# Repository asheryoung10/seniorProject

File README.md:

# Senior Project

## Goal

The goal of this project is to collect high-quality image data from a portable stereo vision device. The recorded data will later be used with a SLAM algorithm to determine the trajectory of the device.

The project is focused on building a complete prototype capable of collecting the sensor data needed for reliable trajectory estimation.

## Current Progress

- Prototype parts have been selected.
- The physical device and housing have been designed and refined through multiple iterations.
- The stereo camera setup has been assembled.
- Stereo image capture is working.
- The data collection software is still being refined.
- Current development is focused on collecting IMU data at the same time as the stereo images without losing capture speed.
- Once reliable data collection is complete, the collected data will be used with a SLAM algorithm to determine the trajectory of the device.

## Prototype

The device is built around a Raspberry Pi and a pair of stereo cameras.

The housing is custom designed to hold the cameras, Raspberry Pi, and other components in a compact package.

## Housing Development

The housing has gone through several design iterations as the physical layout and component placement have been refined.

The final housing is 3D printed and designed using CAD software.

The `CAD` folder contains the FreeCAD project files and 3MF models used to design and manufacture the housing.

## Data Collection

The `Capture` folder contains the software responsible for collecting stereo image and IMU data.

The stereo cameras are used to capture image data while the IMU provides motion information from the device. A major part of the current development is getting both data sources to operate at the same time without significantly reducing the image capture rate.

The folder also contains the camera triggering and `libcamera` configuration used by the stereo camera system.

The goal is to produce consistent, high-quality synchronized data that can later be passed into a SLAM algorithm.

## Viewer

The `Viewer` folder contains software for viewing and inspecting recorded data.

The viewer is used to inspect the captured stereo imagery and verify that the collected data is usable.

## Screen Flash

The `screenFlashBlackWhite` folder contains the software used to control the screen flashing component of the system.

The screen flash is part of the timing and synchronization system used during data collection.

## Project Structure

The repository is organized into the following main components:

- `CAD` contains the FreeCAD project files and 3MF models for the device housing.
- `Capture` contains the stereo camera, IMU, triggering, and data collection software.
- `Pictures` contains project photos, demonstrations, and other visual documentation.
- `Viewer` contains software for viewing and inspecting recorded data.
- `screenFlashBlackWhite` contains the screen flashing software used for synchronization.

## Project Status

The prototype hardware parts have been selected and the physical device is being refined.

The main software task currently underway is improving the data collection system so that IMU data can be collected concurrently with stereo images without sacrificing capture speed.

After the data collection system is sufficiently reliable, the next major stage of the project will be to run a SLAM algorithm on the collected data to estimate the trajectory of the device.

## Pictures
First Model

Superglued together, with cameras that required software rotation and were oriented vertically instead of horizontally.

Handheld demonstration of the old shell with the original viewing software. Capture rate was less than 30 Hz.

Case Development

Multiple case designs were tested before settling on the final clamshell design.

Final Clamshell Design

CAD design of the final device housing.

3D-printed version of the final housing.

Software

Current viewing tool.

Work in progress: rotation collection using the IMU6050.

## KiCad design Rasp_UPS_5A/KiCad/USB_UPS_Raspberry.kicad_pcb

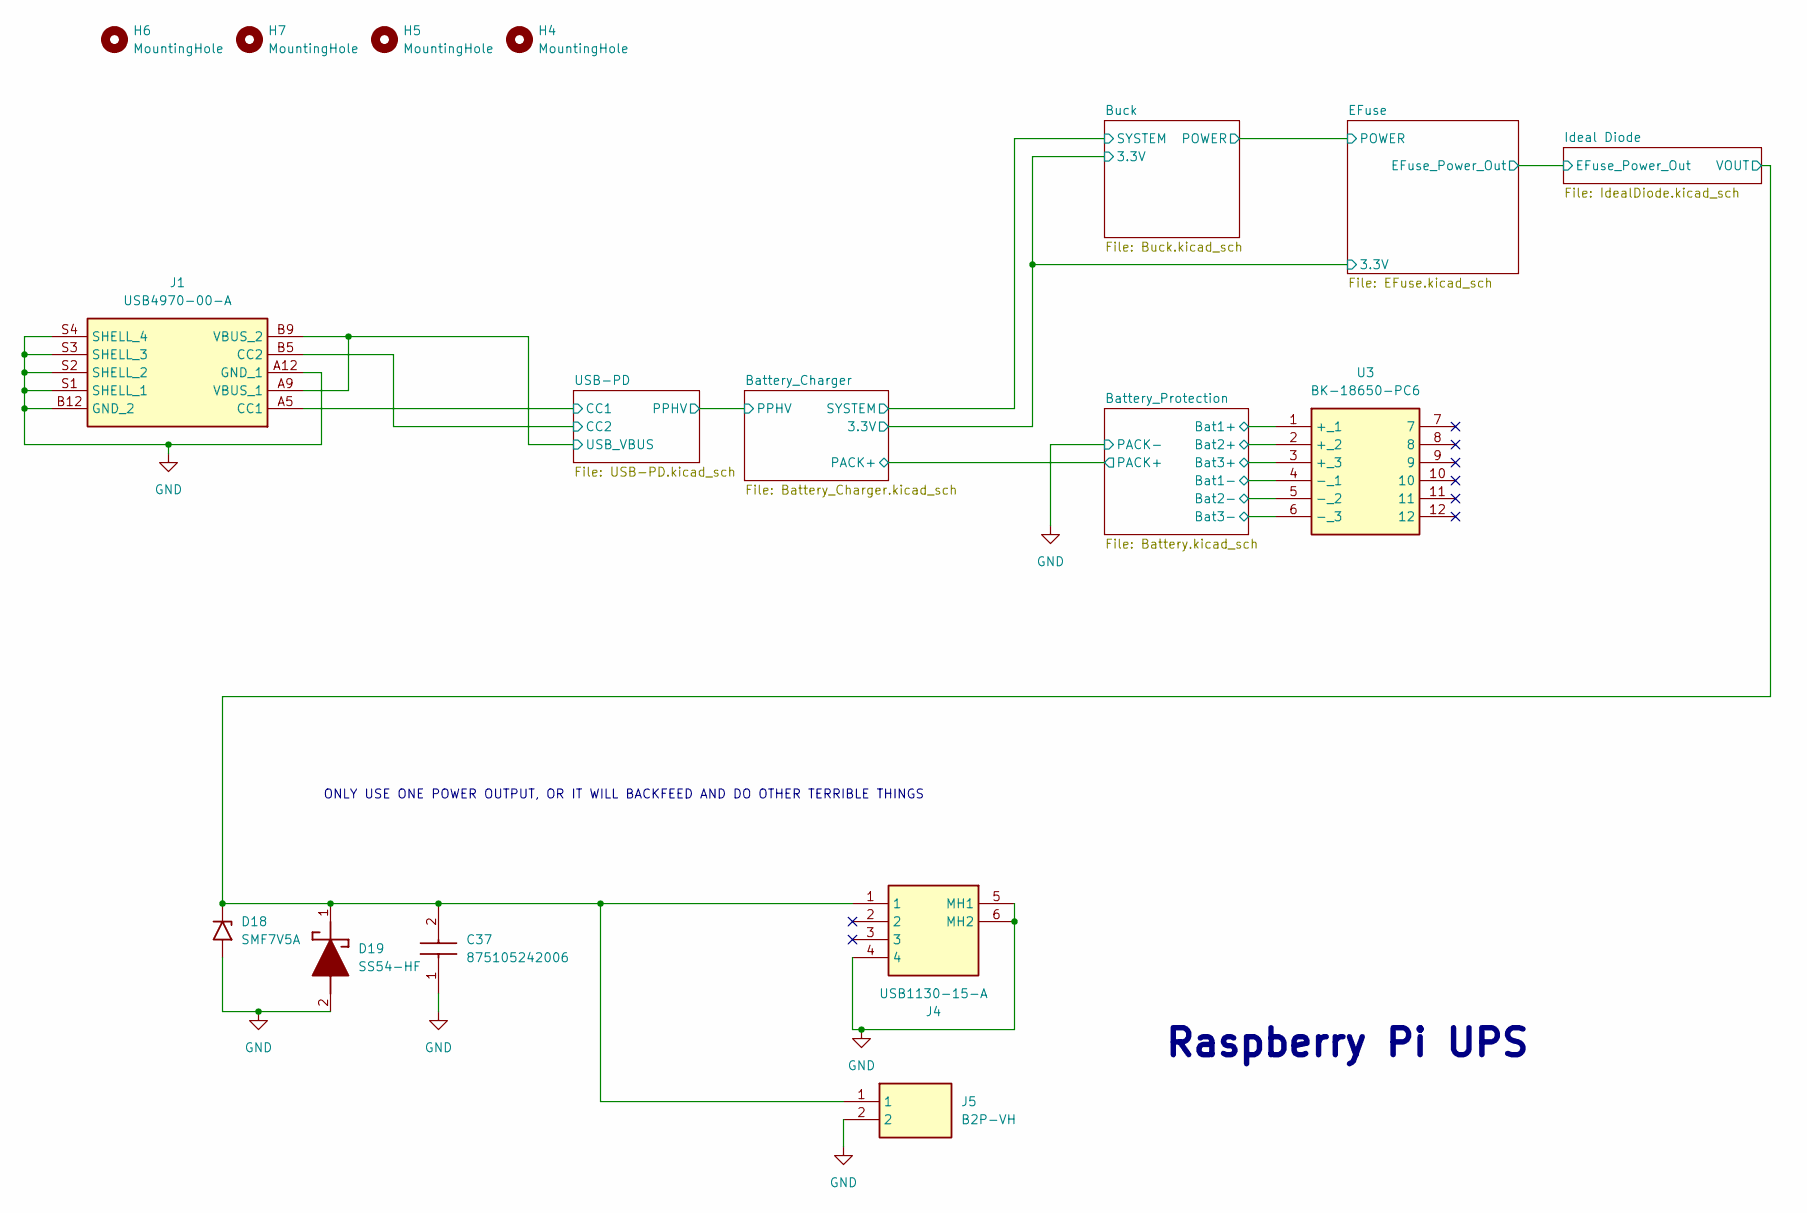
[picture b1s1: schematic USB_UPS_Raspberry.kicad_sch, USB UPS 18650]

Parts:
C37: 875105242006; CAPAE530X550N; Mouser Part Number 710-875105242006
D18: SMF7V5A; D_SMF
D19: SS54-HF; DIOM5025X220N; Mouser Part Number 750-SS54-HF
H4, H5, H6, H7: MountingHole; MountingHole_3.2mm_M3_Pad
J1: USB4970-00-A; USB497000A; Manufacturer_Part_Number USB4970-00-A
J4: USB1130-15-A; USB113015A; Mouser Part Number 640-USB1130-15-A
J5: B2P-VH; SHDR2W114P0X396_1X2_786X850X940P; Manufacturer_Part_Number B2P-VH
U3: BK-18650-PC6; BK18650PC6; Manufacturer_Part_Number BK-18650-PC6

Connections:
-BATT: U3.4 (-_1); also elsewhere on the board
/Battery_Charger/PACK+: U3.3 (+_3); also elsewhere on the board
/Battery_Protection/Bat1+: U3.1 (+_1), U3.5 (-_2); also elsewhere on the board
/Battery_Protection/Bat2+: U3.2 (+_2), U3.6 (-_3); also elsewhere on the board
/Ideal Diode/VOUT: C37.2 (-), D18.1 (A1), D19.1 (K), J4.1, J5.1; also elsewhere on the board
/USB-PD/CC1: J1.A5 (CC1); also elsewhere on the board
/USB-PD/CC2: J1.B5 (CC2); also elsewhere on the board
/USB-PD/VBUS: J1.A9 (VBUS_1), J1.B9 (VBUS_2); also elsewhere on the board
GND: C37.1 (+), D18.2 (A2), D19.2 (A), J1.A12 (GND_1), J1.B12 (GND_2), J1.S1 (SHELL_1), J1.S2 (SHELL_2), J1.S3 (SHELL_3), J1.S4 (SHELL_4), J4.4, J4.5 (MH1), J4.6 (MH2), J5.2; also elsewhere on the board

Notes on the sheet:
ONLY USE ONE POWER OUTPUT, OR IT WILL BACKFEED AND DO OTHER TERRIBLE THINGS
Raspberry Pi UPS

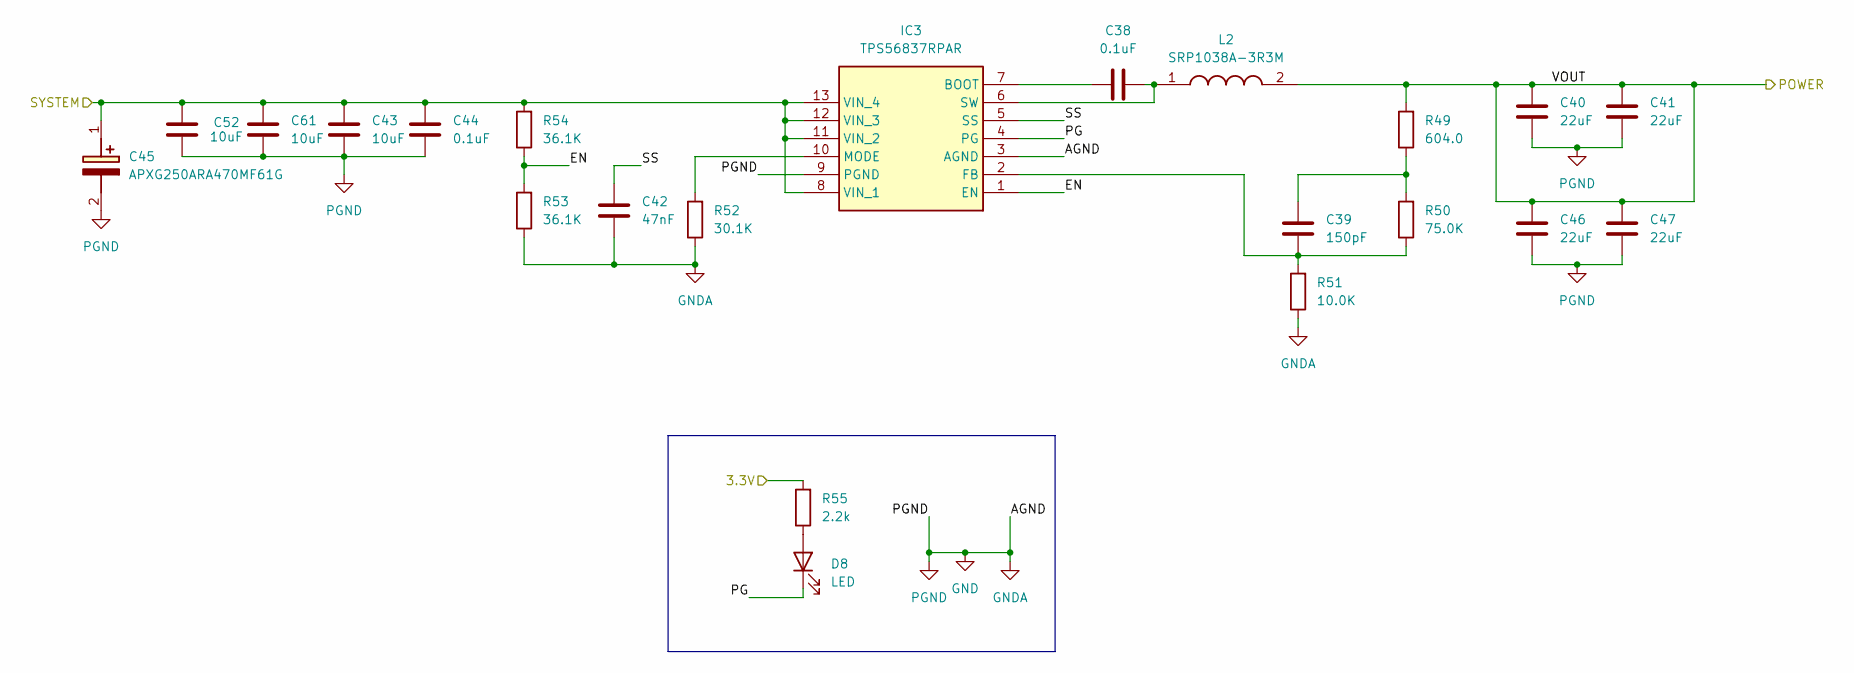
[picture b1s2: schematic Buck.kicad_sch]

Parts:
C38, C44: 0.1uF; C_0805_2012Metric
C39: 150pF; C_0805_2012Metric
C40, C41, C46, C47: 22uF; C_0805_2012Metric
C42: 47nF; C_0805_2012Metric
C43, C52, C61: 10uF; C_0805_2012Metric
C45: APXG250ARA470MF61G; CAPAE660X610N; Manufacturer_Part_Number APXG250ARA470MF61G; Mouser Part Number 661-APXG250A470MF61G
D8: LED; LED_0805_2012Metric
IC3: TPS56837RPAR; TPS56A37RPAR; Mouser Part Number 595-TPS56837RPAR
L2: SRP1038A-3R3M; INDPM110100X400N; Manufacturer_Part_Number SRP1038A-3R3M; Mouser Part Number 652-SRP1038A-3R3M
R49: 604.0; R_0805_2012Metric
R50: 75.0K; R_0805_2012Metric
R51: 10.0K; R_0805_2012Metric
R52: 30.1K; R_0805_2012Metric
R53, R54: 36.1K; R_0805_2012Metric
R55: 2.2k; R_0805_2012Metric

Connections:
/Battery_Charger/SYSTEM: C43.1, C44.1, C45.1 (+), C52.1, C61.1, IC3.8 (VIN_1), IC3.11 (VIN_2), IC3.12 (VIN_3), IC3.13 (VIN_4), R54.2; also elsewhere on the board
/Battery_Charger/VREF: R55.2; also elsewhere on the board
/Buck/EN: IC3.1 (EN), R53.2, R54.1
/Buck/PG: D8.1 (K), IC3.4 (PG)
/Buck/SS: C42.1, IC3.5 (SS)
/Buck/VOUT: C40.2, C41.2, C46.2, C47.2, L2.2, R49.2; also elsewhere on the board
GND: C40.1, C41.1, C42.2, C43.2, C44.2, C45.2 (-), C46.1, C47.1, C52.2, C61.2, IC3.3 (AGND), IC3.9 (PGND), R51.1, R52.1, R53.1; also elsewhere on the board
unnamed: C39.2, R49.1, R50.2
unnamed: D8.2 (A), R55.1
unnamed: C38.1, IC3.7 (BOOT)
unnamed: C39.1, IC3.2 (FB), R50.1, R51.2
unnamed: IC3.10 (MODE), R52.2
unnamed: C38.2, IC3.6 (SW), L2.1

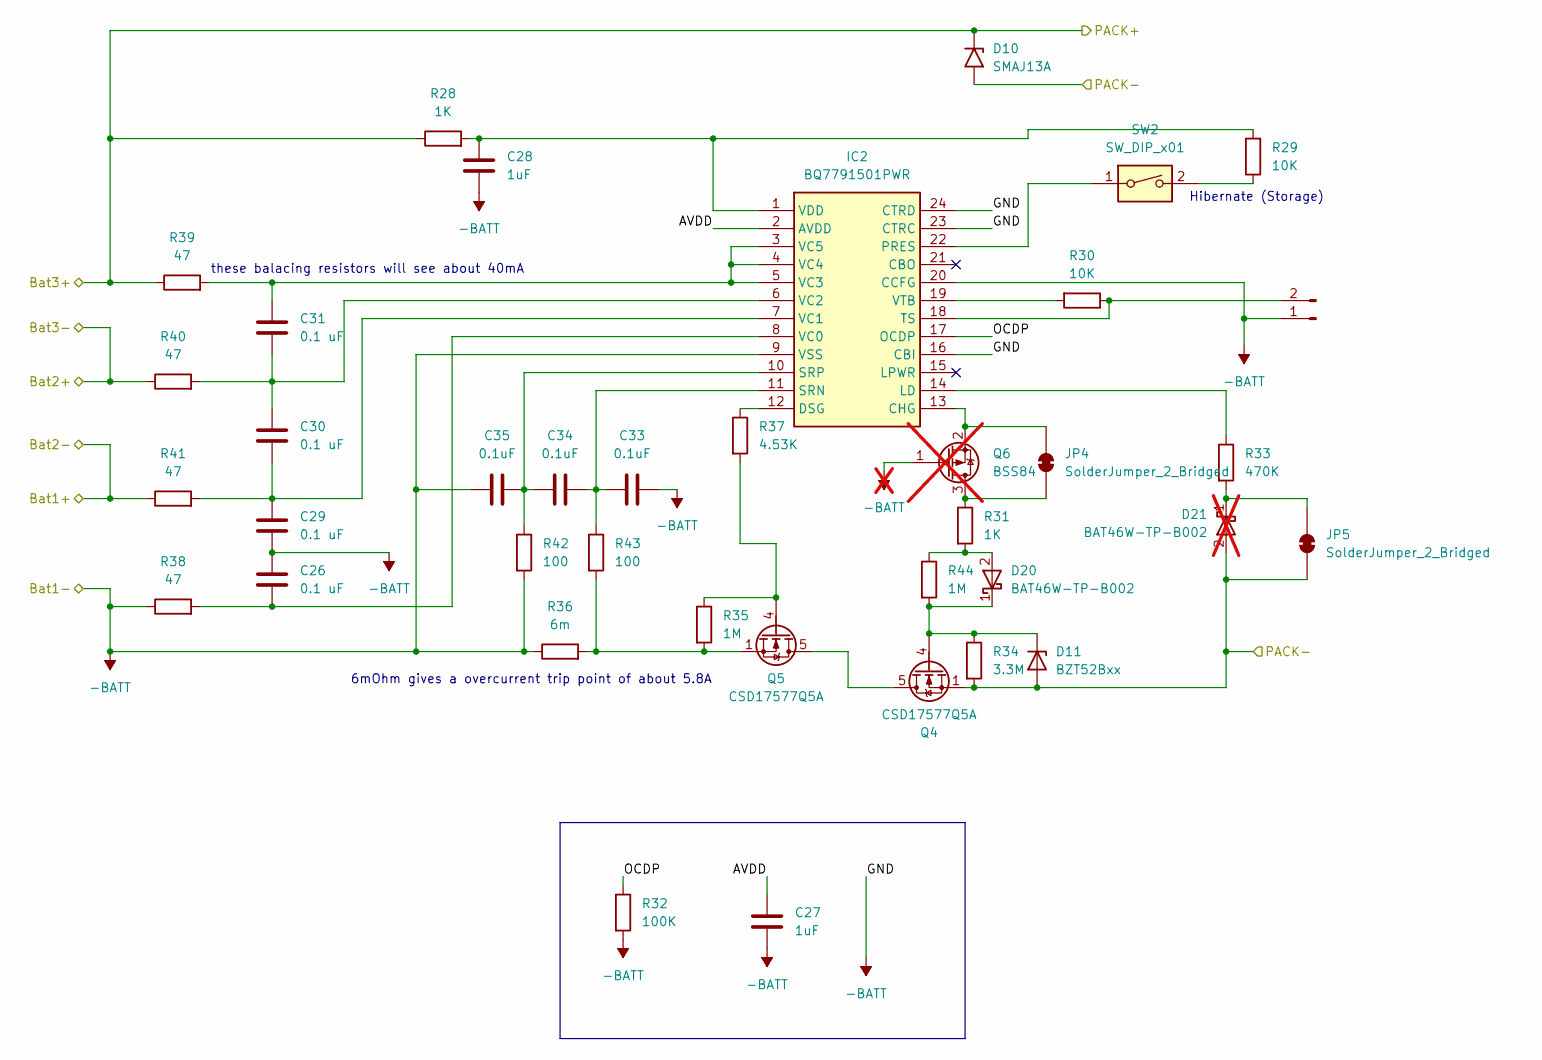
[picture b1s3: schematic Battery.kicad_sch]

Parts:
C26, C29, C30, C31: 0.1 uF; C_0805_2012Metric
C27, C28: 1uF; C_0805_2012Metric
C33, C34, C35: 0.1uF; C_0805_2012Metric
D10: SMAJ13A; D_SMA
D11: BZT52Bxx; D_SOD-123F
D20: BAT46W-TP-B002; SOD3716X135N; Manufacturer_Part_Number BAT46W-TP-B002
D21: BAT46W-TP-B002; SOD3716X135N; Manufacturer_Part_Number BAT46W-TP-B002; not fitted
IC2: BQ7791501PWR; SOP65P640X120-24N; Mouser Part Number 595-BQ7791501PWR
J3: Conn_01x02_Pin; PinHeader_1x02_P2.54mm_Vertical
JP4, JP5: SolderJumper_2_Bridged; SolderJumper-2_P1.3mm_Bridged_Pad1.0x1.5mm
Q4, Q5: CSD17577Q5A; TDSON-8-1
Q6: BSS84; SOT-23; not fitted
R28, R31: 1K; R_0805_2012Metric
R29, R30: 10K; R_0805_2012Metric
R32: 100K; R_0805_2012Metric
R33: 470K; R_0805_2012Metric
R34: 3.3M; R_0805_2012Metric
R35, R44: 1M; R_0805_2012Metric
R36: 6m; R_1206_3216Metric
R37: 4.53K; R_0805_2012Metric
R38, R39, R40, R41: 47; R_1206_3216Metric
R42, R43: 100; R_0805_2012Metric
SW2: SW_DIP_x01; SW_DIP_SPSTx01_Slide_6.7x4.1mm_W7.62mm_P2.54mm_LowProfile

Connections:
-BATT: C26.1, C27.2, C28.2, C29.2, C33.2, C35.1, IC2.9 (VSS), IC2.16 (CBI), IC2.20 (CCFG), IC2.23 (CTRC), IC2.24 (CTRD), J3.1, Q6.1 (G), R32.2, R36.1, R38.1, R42.2; also elsewhere on the board
/Battery_Charger/PACK+: D10.1 (A1), R28.1, R39.1; also elsewhere on the board
/Battery_Protection/AVDD: C27.1, IC2.2 (AVDD)
/Battery_Protection/Bat1+: R41.1; also elsewhere on the board
/Battery_Protection/Bat2+: R40.1; also elsewhere on the board
/Battery_Protection/OCDP: IC2.17 (OCDP), R32.1
GND: D10.2 (A2), D11.2 (A), D21.2 (A), JP5.1 (A), Q4.1 (S), Q4.2 (S), Q4.3 (S), R34.2; also elsewhere on the board
unnamed: D11.1 (K), D20.1 (K), Q4.4 (G), R34.1, R44.2
unnamed: D20.2 (A), R31.2, R44.1
unnamed: D21.1 (K), JP5.2 (B), R33.2
unnamed: IC2.13 (CHG), JP4.2 (B), Q6.2 (S)
unnamed: IC2.12 (DSG), R37.1
unnamed: IC2.14 (LD), R33.1
unnamed: IC2.22 (PRES), SW2.1
unnamed: C33.1, C34.2, IC2.11 (SRN), R43.1
unnamed: C34.1, C35.2, IC2.10 (SRP), R42.1
unnamed: IC2.18 (TS), J3.2, R30.1
unnamed: C26.2, IC2.8 (VC0), R38.2
unnamed: C29.1, C30.2, IC2.7 (VC1), R41.2
unnamed: C30.1, C31.2, IC2.6 (VC2), R40.2
unnamed: C31.1, IC2.3 (VC5), IC2.4 (VC4), IC2.5 (VC3), R39.2
unnamed: C28.1, IC2.1 (VDD), R28.2, R29.2
unnamed: IC2.19 (VTB), R30.2
unnamed: JP4.1 (A), Q6.3 (D), R31.1
unnamed: Q4.5 (D), Q5.5 (D)
unnamed: Q5.4 (G), R35.1, R37.2
unnamed: Q5.1 (S), Q5.2 (S), Q5.3 (S), R35.2, R36.2, R43.2
unnamed: R29.1, SW2.2

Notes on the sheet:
Hibernate (Storage)
these balacing resistors will see about 40mA
6mOhm gives a overcurrent trip point of about 5.8A

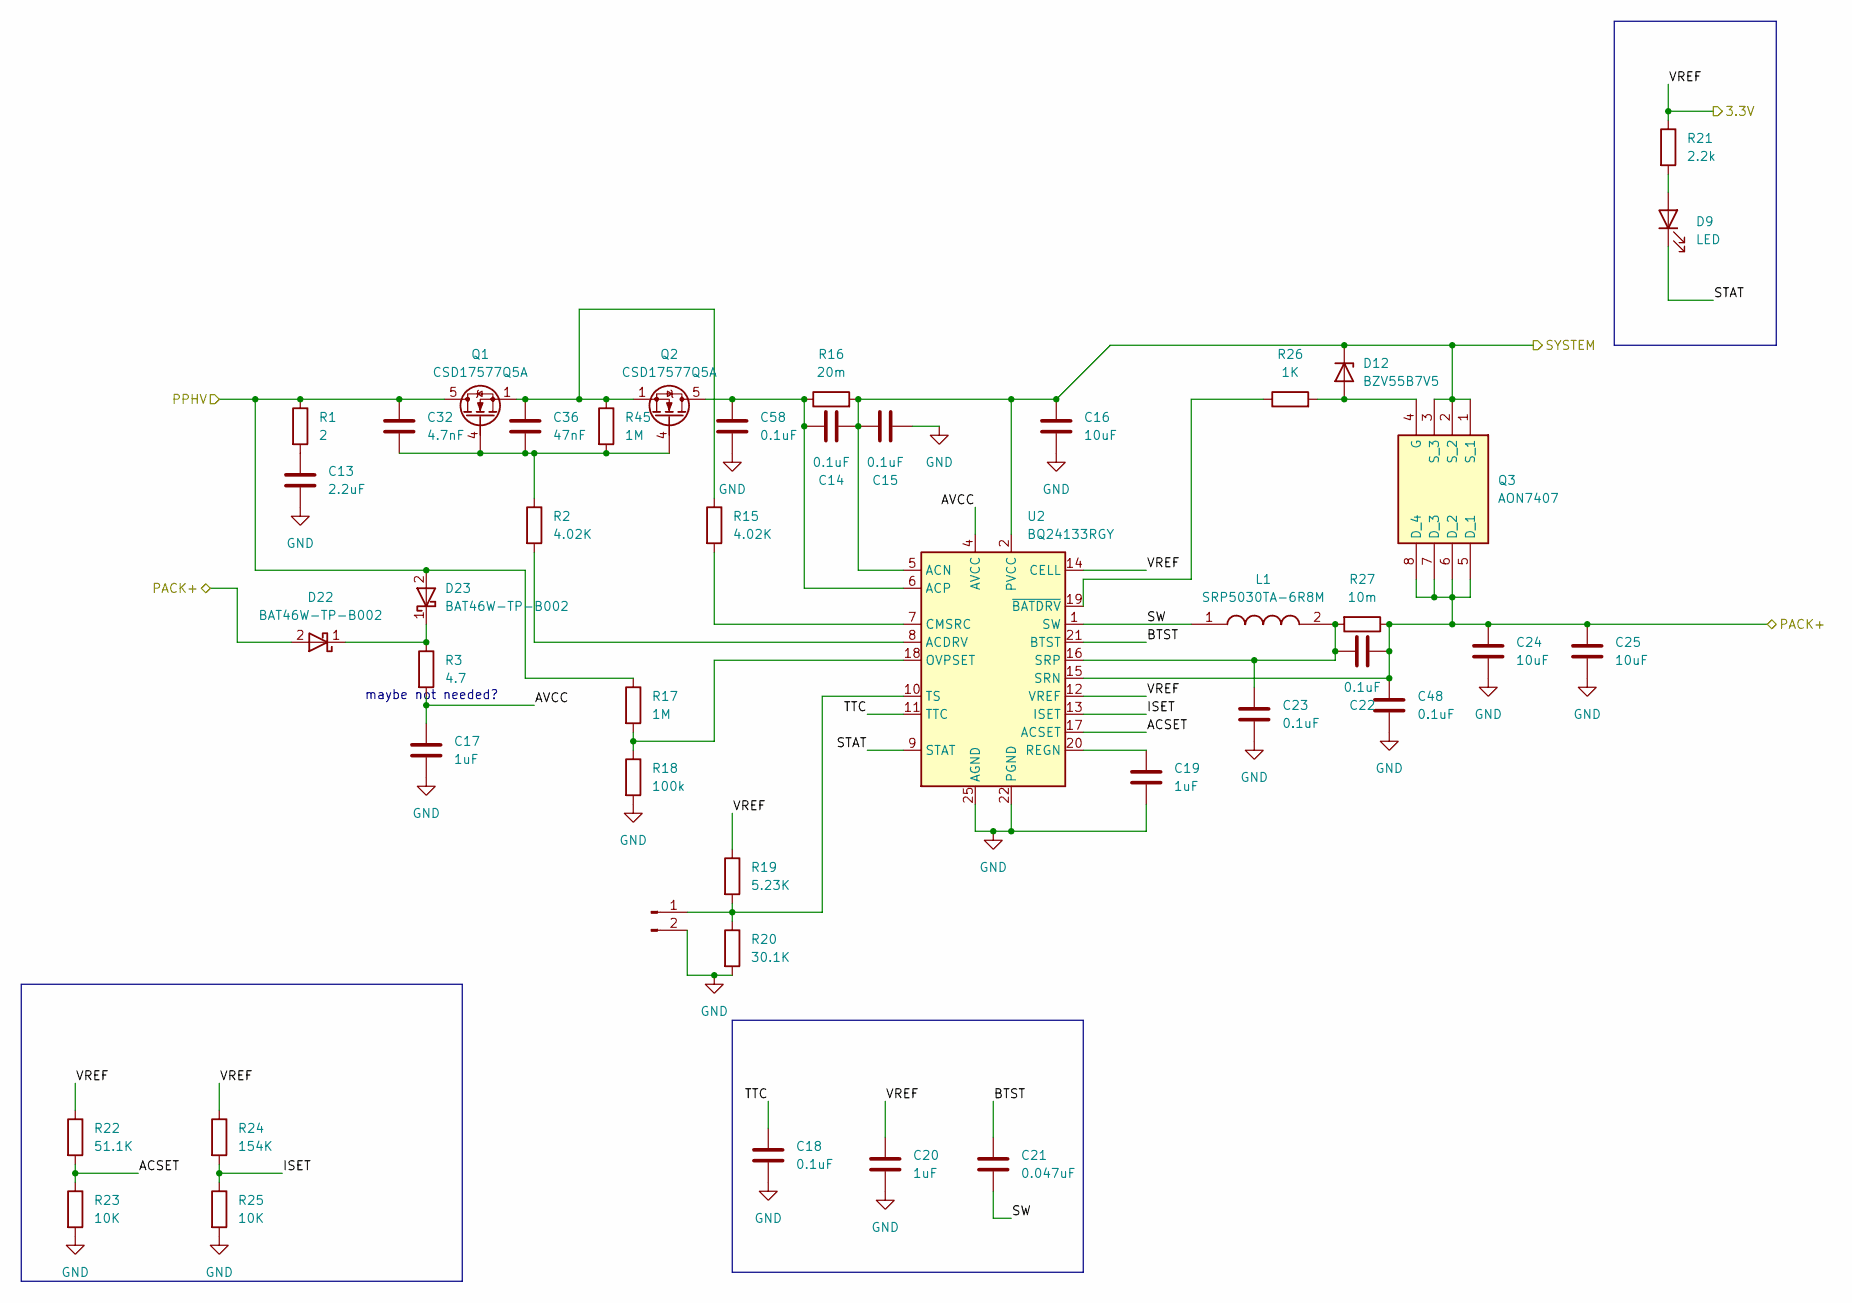
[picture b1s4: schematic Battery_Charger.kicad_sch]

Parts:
C13: 2.2uF; C_0805_2012Metric
C14, C15, C18, C22, C23, C48, C58: 0.1uF; C_0805_2012Metric
C16, C24, C25: 10uF; C_0805_2012Metric
C17, C19, C20: 1uF; C_0805_2012Metric
C21: 0.047uF; C_0805_2012Metric
C32: 4.7nF; C_0805_2012Metric
C36: 47nF; C_0805_2012Metric
D9: LED; LED_0805_2012Metric
D12: BZV55B7V5; D_MiniMELF
D22, D23: BAT46W-TP-B002; SOD3716X135N; Manufacturer_Part_Number BAT46W-TP-B002
J2: Conn_01x02_Pin; PinHeader_1x02_P2.54mm_Vertical
L1: SRP5030TA-6R8M; INDPM5752X300N; Manufacturer_Part_Number SRP5030TA-6R8M; Mouser Part Number 652-SRP5030TA-6R8M
Q1, Q2: CSD17577Q5A; TDSON-8-1
Q3: AON7407; DFN_3X3_EP; Manufacturer_Part_Number AON7407
R1: 2; R_0805_2012Metric
R2, R15: 4.02K; R_0805_2012Metric
R3: 4.7; R_0805_2012Metric
R16: 20m; R_1206_3216Metric
R17, R45: 1M; R_0805_2012Metric
R18: 100k; R_0805_2012Metric
R19: 5.23K; R_0805_2012Metric
R20: 30.1K; R_0805_2012Metric
R21: 2.2k; R_0805_2012Metric
R22: 51.1K; R_0805_2012Metric
R23, R25: 10K; R_0805_2012Metric
R24: 154K; R_0805_2012Metric
R26: 1K; R_0805_2012Metric
R27: 10m; R_1206_3216Metric
U2: BQ24133RGY; Texas_RGY_R-PVQFN-N24_EP2.05x3.1mm

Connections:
/Battery_Charger/ACSET: R22.2, R23.1, U2.17 (ACSET)
/Battery_Charger/AVCC: C17.1, R3.2, U2.4 (AVCC)
/Battery_Charger/BTST: C21.1, U2.21 (BTST)
/Battery_Charger/ISET: R24.2, R25.1, U2.13 (ISET)
/Battery_Charger/PACK+: C22.2, C24.2, C25.2, C48.2, D22.2 (A), Q3.5 (D_1), Q3.6 (D_2), Q3.7 (D_3), Q3.8 (D_4), Q3.9, Q3.10, Q3.11, R27.1, U2.15 (SRN); also elsewhere on the board
/Battery_Charger/STAT: D9.1 (K), U2.9 (STAT)
/Battery_Charger/SW: C21.2, L1.1, U2.1 (SW), U2.24 (SW)
/Battery_Charger/SYSTEM: C14.2, C15.1, C16.1, D12.1 (K), Q3.1 (S_1), Q3.2 (S_2), Q3.3 (S_3), R16.2, U2.2 (PVCC), U2.3 (PVCC), U2.5 (ACN); also elsewhere on the board
/Battery_Charger/TTC: C18.1, U2.11 (TTC)
/Battery_Charger/VREF: C20.1, R19.1, R21.1, R22.1, R24.1, U2.12 (VREF), U2.14 (CELL); also elsewhere on the board
/USB-PD/PPHV: C32.1, D23.2 (A), Q1.5 (D), R1.1, R17.1; also elsewhere on the board
GND: C13.2, C15.2, C16.2, C17.2, C18.2, C19.2, C20.2, C23.1, C24.1, C25.1, C48.1, C58.1, J2.2, R18.2, R20.2, R23.2, R25.2, U2.22 (PGND), U2.23 (PGND), U2.25 (AGND); also elsewhere on the board
unnamed: C13.1, R1.2
unnamed: C36.1, Q1.1 (S), Q1.2 (S), Q1.3 (S), Q2.1 (S), Q2.2 (S), Q2.3 (S), R15.1, R45.1
unnamed: D9.2 (A), R21.2
unnamed: D12.2 (A), Q3.4 (G), R26.2
unnamed: D22.1 (K), D23.1 (K), R3.1
unnamed: J2.1, R19.2, R20.1, U2.10 (TS)
unnamed: C32.2, C36.2, Q1.4 (G), Q2.4 (G), R2.1, R45.2
unnamed: C14.1, C58.2, Q2.5 (D), R16.1, U2.6 (ACP)
unnamed: R2.2, U2.8 (ACDRV)
unnamed: R15.2, U2.7 (CMSRC)
unnamed: R17.2, R18.1, U2.18 (OVPSET)
unnamed: C19.1, U2.20 (REGN)
unnamed: C22.1, C23.2, L1.2, R27.2, U2.16 (SRP)
unnamed: R26.1, U2.19 (~BATDRV)

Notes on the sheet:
maybe not needed?

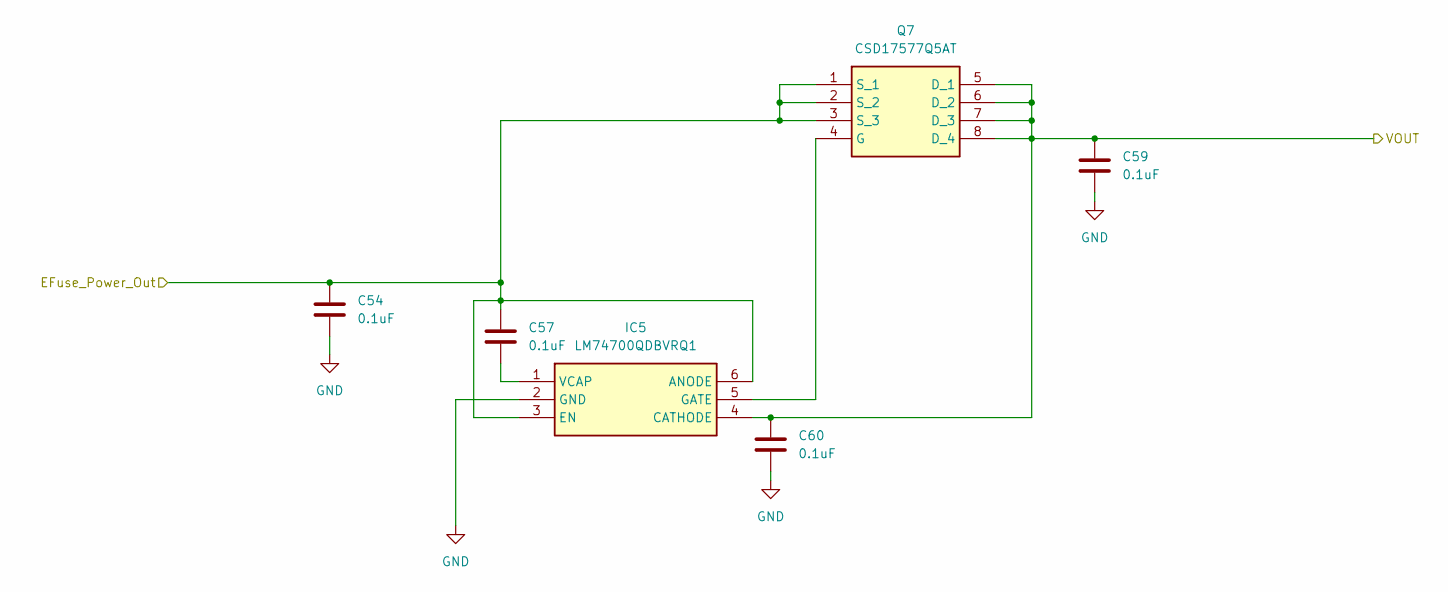
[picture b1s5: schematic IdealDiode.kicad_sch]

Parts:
C54, C57, C59, C60: 0.1uF; C_0805_2012Metric
IC5: LM74700QDBVRQ1; SOT95P280X145-6N; Mouser Part Number 595-LM74700QDBVRQ1
Q7: CSD17577Q5AT; CSD17310Q5A; Manufacturer_Part_Number CSD17577Q5AT; Mouser Part Number 595-CSD17577Q5AT

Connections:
/EFuse/EFuse_Power_Out: C54.1, C57.1, IC5.3 (EN), IC5.6 (ANODE), Q7.1 (S_1), Q7.2 (S_2), Q7.3 (S_3); also elsewhere on the board
/Ideal Diode/VOUT: C59.1, C60.1, IC5.4 (CATHODE), Q7.5 (D_1), Q7.6 (D_2), Q7.7 (D_3), Q7.8 (D_4), Q7.9; also elsewhere on the board
GND: C54.2, C59.2, C60.2, IC5.2 (GND); also elsewhere on the board
unnamed: IC5.5 (GATE), Q7.4 (G)
unnamed: C57.2, IC5.1 (VCAP)

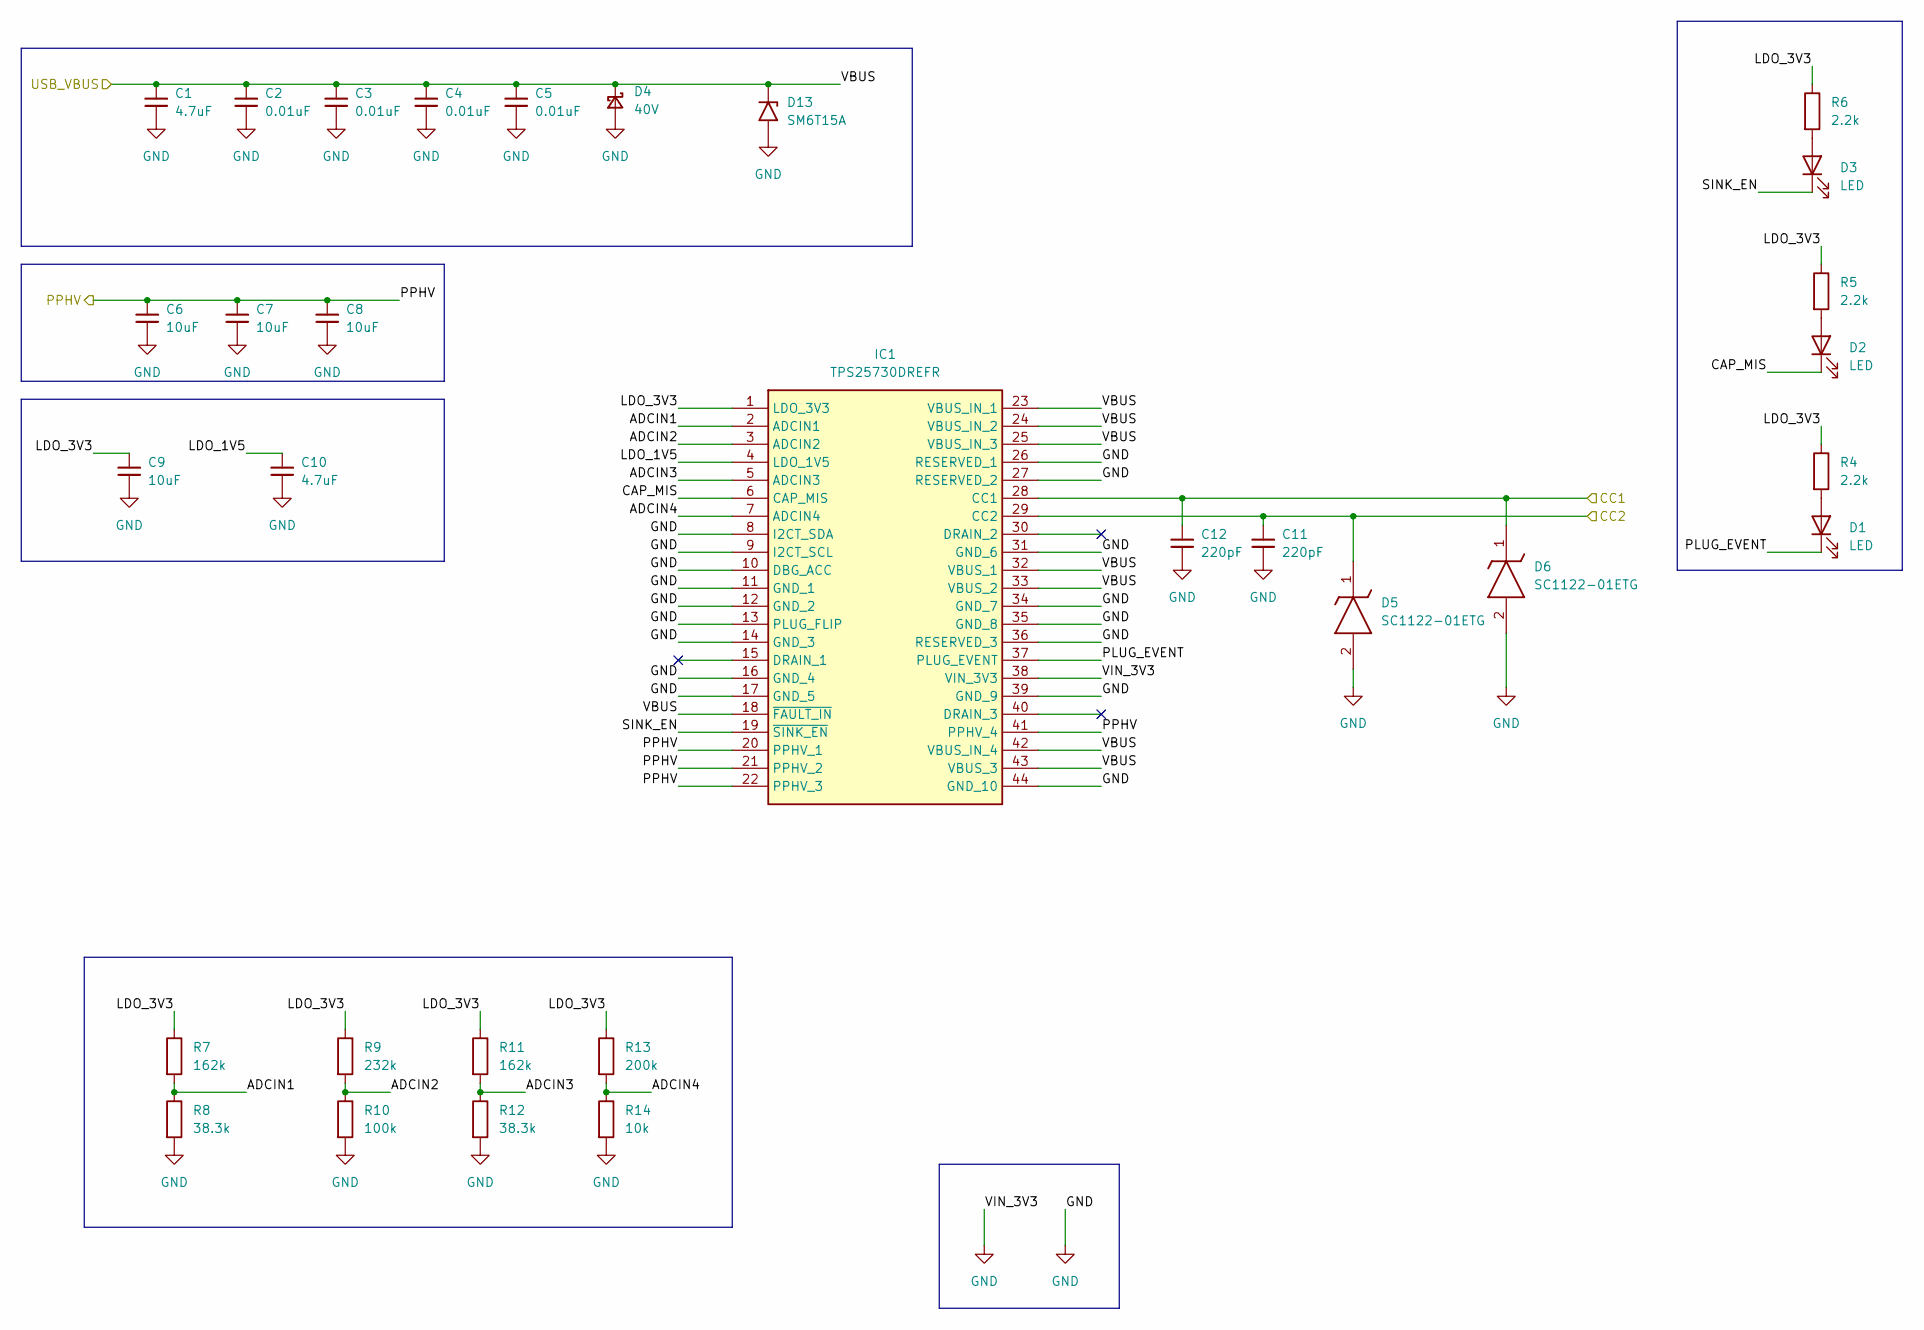
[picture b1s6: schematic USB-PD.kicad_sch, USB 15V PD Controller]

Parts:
C1, C10: 4.7uF; C_0805_2012Metric
C2, C3, C4, C5: 0.01uF; C_0805_2012Metric
C6, C7, C8, C9: 10uF; C_0805_2012Metric
C11, C12: 220pF; C_0805_2012Metric
D1, D2, D3: LED; LED_0805_2012Metric
D4: 40V; D_SMA_Handsoldering
D5, D6: SC1122-01ETG; SC112201ETG; Manufacturer_Part_Number SC1122-01ETG
D13: SM6T15A; D_SMB
IC1: TPS25730DREFR; Mouser Part Number 595-TPS25730DREFR
R4, R5, R6: 2.2k; R_0805_2012Metric
R7, R11: 162k; R_0805_2012Metric
R8, R12: 38.3k; R_0805_2012Metric
R9: 232k; R_0805_2012Metric
R10: 100k; R_0805_2012Metric
R13: 200k; R_0805_2012Metric
R14: 10k; R_0805_2012Metric

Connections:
/USB-PD/ADCIN1: IC1.2 (ADCIN1), R7.2, R8.1
/USB-PD/ADCIN2: IC1.3 (ADCIN2), R9.2, R10.1
/USB-PD/ADCIN3: IC1.5 (ADCIN3), R11.2, R12.1
/USB-PD/ADCIN4: IC1.7 (ADCIN4), R13.2, R14.1
/USB-PD/CAP_MIS: D2.1 (K), IC1.6 (CAP_MIS)
/USB-PD/CC1: C12.1, D6.1 (K), IC1.28 (CC1); also elsewhere on the board
/USB-PD/CC2: C11.1, D5.1 (K), IC1.29 (CC2); also elsewhere on the board
/USB-PD/LDO_1V5: C10.1, IC1.4 (LDO_1V5)
/USB-PD/LDO_3V3: C9.1, IC1.1 (LDO_3V3), R4.1, R5.1, R6.1, R7.1, R9.1, R11.1, R13.1
/USB-PD/PLUG_EVENT: D1.1 (K), IC1.37 (PLUG_EVENT)
/USB-PD/PPHV: C6.1, C7.1, C8.1, IC1.20 (PPHV_1), IC1.21 (PPHV_2), IC1.22 (PPHV_3), IC1.41 (PPHV_4); also elsewhere on the board
/USB-PD/SINK_EN: D3.1 (K), IC1.19 (~SINK_EN)
/USB-PD/VBUS: C1.1, C2.1, C3.1, C4.1, C5.1, D4.1 (K), D13.1 (A1), IC1.18 (~FAULT_IN), IC1.23 (VBUS_IN_1), IC1.24 (VBUS_IN_2), IC1.25 (VBUS_IN_3), IC1.32 (VBUS_1), IC1.33 (VBUS_2), IC1.42 (VBUS_IN_4), IC1.43 (VBUS_3); also elsewhere on the board
GND: C1.2, C2.2, C3.2, C4.2, C5.2, C6.2, C7.2, C8.2, C9.2, C10.2, C11.2, C12.2, D4.2 (A), D5.2 (A), D6.2 (A), D13.2 (A2), IC1.8 (I2CT_SDA), IC1.9 (I2CT_SCL), IC1.10 (DBG_ACC), IC1.11 (GND_1), IC1.12 (GND_2), IC1.13 (PLUG_FLIP), IC1.14 (GND_3), IC1.16 (GND_4), IC1.17 (GND_5), IC1.26 (RESERVED_1), IC1.27 (RESERVED_2), IC1.31 (GND_6), IC1.34 (GND_7), IC1.35 (GND_8), IC1.36 (RESERVED_3), IC1.38 (VIN_3V3), IC1.39 (GND_9), IC1.44 (GND_10), R8.2, R10.2, R12.2, R14.2; also elsewhere on the board
unnamed: D1.2 (A), R4.2
unnamed: D2.2 (A), R5.2
unnamed: D3.2 (A), R6.2

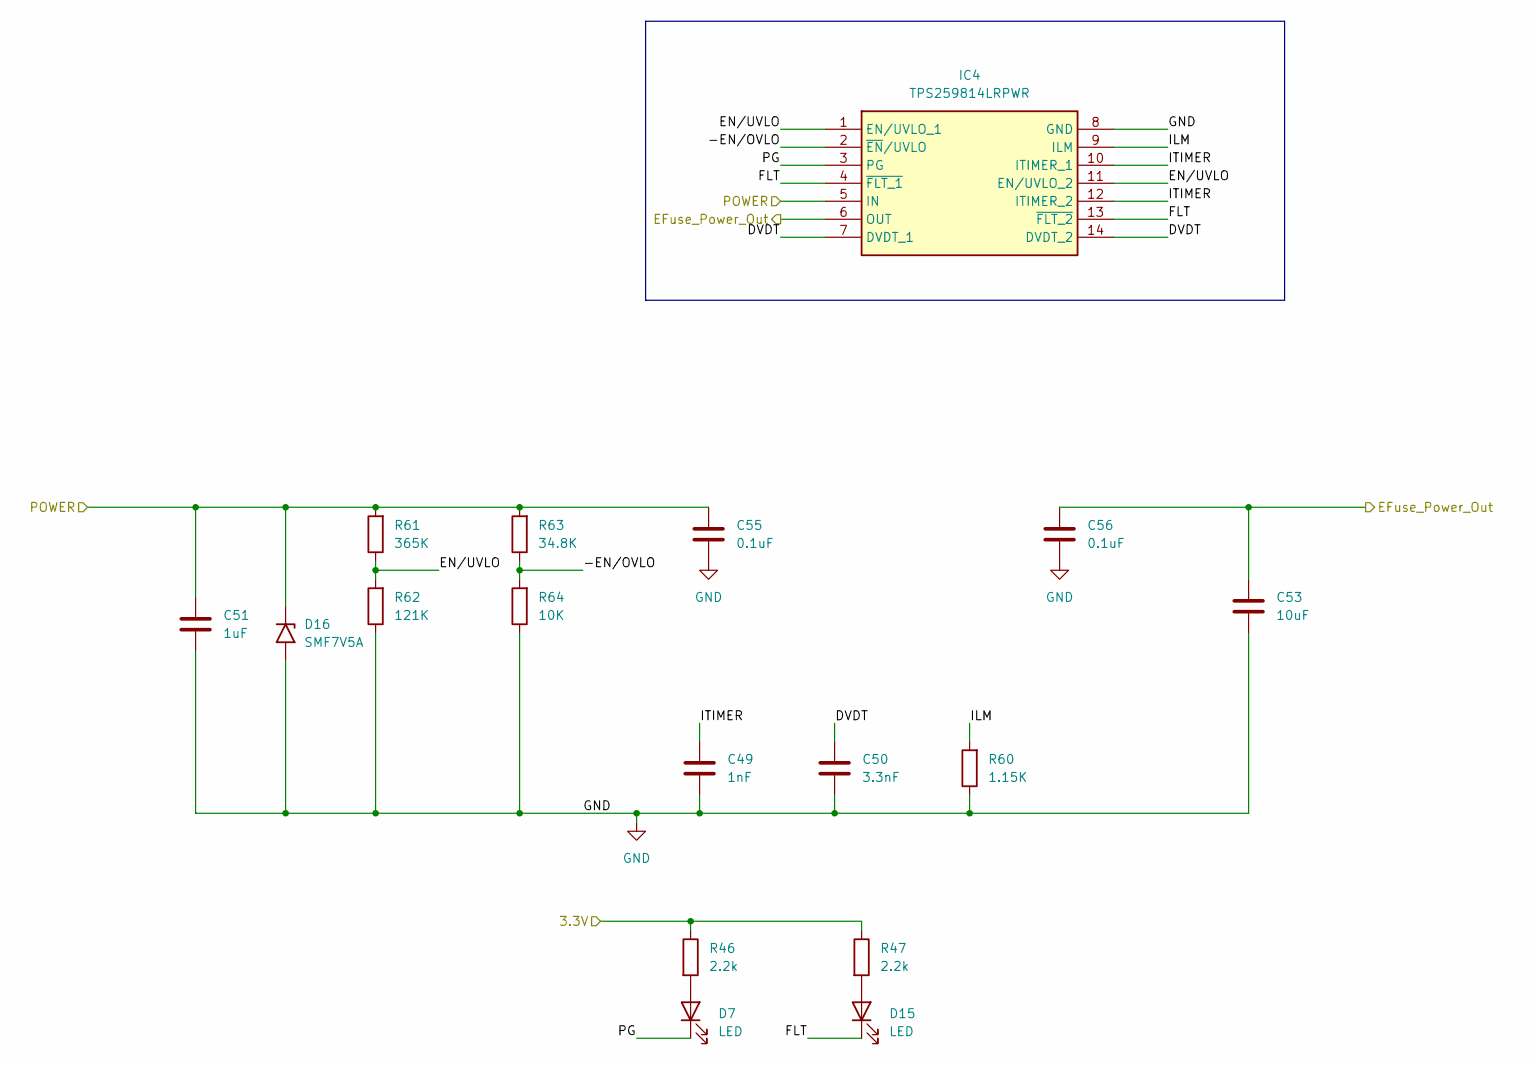
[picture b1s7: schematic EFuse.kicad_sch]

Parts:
C49: 1nF; C_0805_2012Metric
C50: 3.3nF; C_0805_2012Metric
C51: 1uF; C_0805_2012Metric
C53: 10uF; C_0805_2012Metric
C55, C56: 0.1uF; C_0805_2012Metric
D7, D15: LED; LED_0805_2012Metric
D16: SMF7V5A; D_SMF
IC4: TPS259814LRPWR; TPS259470ARPWR; Manufacturer_Part_Number TPS259814LRPWR
R46, R47: 2.2k; R_0805_2012Metric
R60: 1.15K; R_0805_2012Metric
R61: 365K; R_0805_2012Metric
R62: 121K; R_0805_2012Metric
R63: 34.8K; R_0805_2012Metric
R64: 10K; R_0805_2012Metric

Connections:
/Battery_Charger/VREF: R46.1, R47.1; also elsewhere on the board
/Buck/VOUT: C51.2, C55.2, D16.1 (A1), IC4.5 (IN), R61.2, R63.2; also elsewhere on the board
/EFuse/-EN/OVLO: IC4.2 (~EN/UVLO), R63.1, R64.2
/EFuse/DVDT: C50.2, IC4.7 (DVDT_1), IC4.14 (DVDT_2)
/EFuse/EFuse_Power_Out: C53.2, C56.2, IC4.6 (OUT); also elsewhere on the board
/EFuse/EN/UVLO: IC4.1 (EN/UVLO_1), IC4.11 (EN/UVLO_2), R61.1, R62.2
/EFuse/FLT: D15.1 (K), IC4.4 (~FLT_1), IC4.13 (~FLT_2)
/EFuse/ILM: IC4.9 (ILM), R60.2
/EFuse/ITIMER: C49.2, IC4.10 (ITIMER_1), IC4.12 (ITIMER_2)
/EFuse/PG: D7.1 (K), IC4.3 (PG)
GND: C49.1, C50.1, C51.1, C53.1, C55.1, C56.1, D16.2 (A2), IC4.8 (GND), R60.1, R62.1, R64.1; also elsewhere on the board
unnamed: D7.2 (A), R46.2
unnamed: D15.2 (A), R47.2
